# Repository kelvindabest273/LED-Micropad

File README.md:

# LED Micropad
This is a macropad that has 3 keys (Num Lock, Caps Lock, and Scroll Lock), 3 LED indicators for the aforementioned, and a 0.91 inch 128x32 OLED screen that also, you guessed it, shows the status of aforementioned keys!

Render of the macropad:

Front of the case:

Back of the case:

Schematic:

PCB Layout:

BOM: \
1x Seeed XIAO RP2040 \
3x SK6812MINI-E LEDs \
1x EC11 Rotary Encoder \
1x 0.91 OLED 128x32 screen \
3x Cherry MX-style switches \
1x PCB (not sure if this should be included) \
1x 3D Printed Case (not sure if this should be included)

# Resources that I used to help me make this:
I used help from ChatGPT (before you get mad some of this code was like reading an ancient language) \
https://files.seeedstudio.com/wiki/XIAO-RP2040/res/Seeed-Studio-XIAO-RP2040-v1.3.pdf (this one especially) \
https://github.com/HEofOttoman/hackpadbludprintmacro/blob/main/firmware/henrywausbloodyhackbludpad/keyboard.json (and this too) \
https://github.com/hackclub/hackpad/blob/clean/extras/orpheuspad/firmware/QMK/rules.mk \
https://docs.qmk.fm/config_options \
https://docs.qmk.fm/features/oled_driver \
https://docs.qmk.fm/features/led_indicators \
https://docs.qmk.fm/custom_quantum_functions \
https://docs.qmk.fm/features/rgb_matrix \
https://docs.qmk.fm/drivers/ws2812 \
https://docs.qmk.fm/data_driven_config \
https://github.com/Keychron/qmk_firmware/tree/2025q3/keyboards/keychron/v3/ansi/keymaps (just look around here, tho you might not find much here)

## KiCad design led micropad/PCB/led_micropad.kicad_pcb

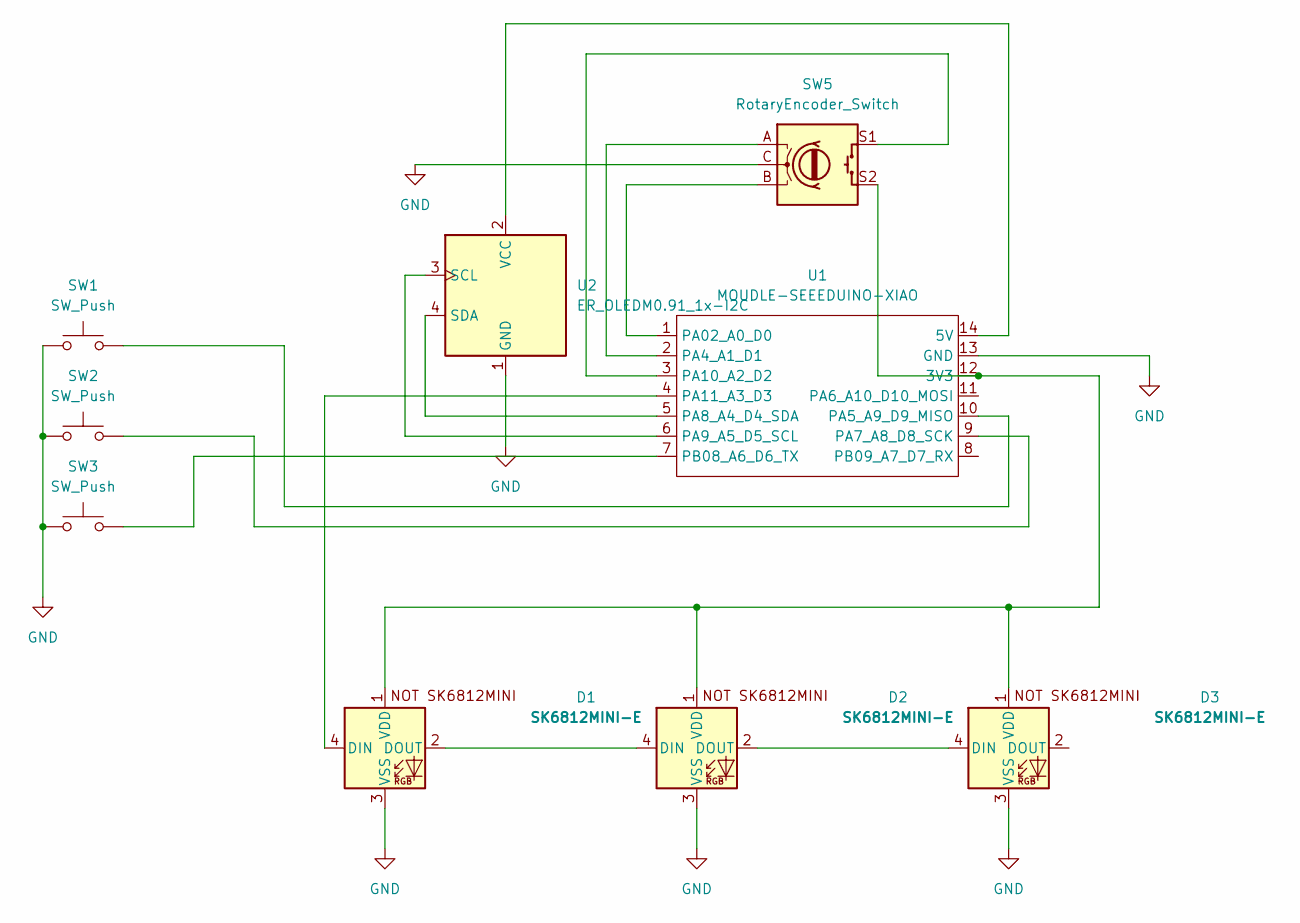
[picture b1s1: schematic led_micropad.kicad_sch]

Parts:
D1, D2, D3: SK6812MINI-E; SK6812MINI-E_fixed
SW1, SW2, SW3: SW_Push; SW_Cherry_MX_1.00u_PCB
SW5: RotaryEncoder_Switch; RotaryEncoder_Alps_EC11E-Switch_Vertical_H20mm
U1: MOUDLE-SEEEDUINO-XIAO; XIAO-Generic-Hybrid-14P-2.54-21X17.8MM
U2: ER_OLEDM0.91_1x-I2C

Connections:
GND: D1.3 (VSS), D2.3 (VSS), D3.3 (VSS), SW1.1, SW2.1, SW3.1, SW5.C, U1.13 (GND), U2.1 (GND)
unnamed: D1.4 (DIN), U1.4 (PA11_A3_D3)
unnamed: D1.2 (DOUT), D2.4 (DIN)
unnamed: D1.1 (VDD), D2.1 (VDD), D3.1 (VDD), SW5.S2, U1.12 (3V3)
unnamed: D2.2 (DOUT), D3.4 (DIN)
unnamed: U1.14 (5V), U2.2 (VCC)
unnamed: SW5.B, U1.1 (PA02_A0_D0)
unnamed: SW5.A, U1.2 (PA4_A1_D1)
unnamed: SW1.2, U1.10 (PA5_A9_D9_MISO)
unnamed: SW2.2, U1.9 (PA7_A8_D8_SCK)
unnamed: U1.5 (PA8_A4_D4_SDA), U2.4 (SDA)
unnamed: U1.6 (PA9_A5_D5_SCL), U2.3 (SCL)
unnamed: SW5.S1, U1.3 (PA10_A2_D2)
unnamed: SW3.2, U1.7 (PB08_A6_D6_TX)

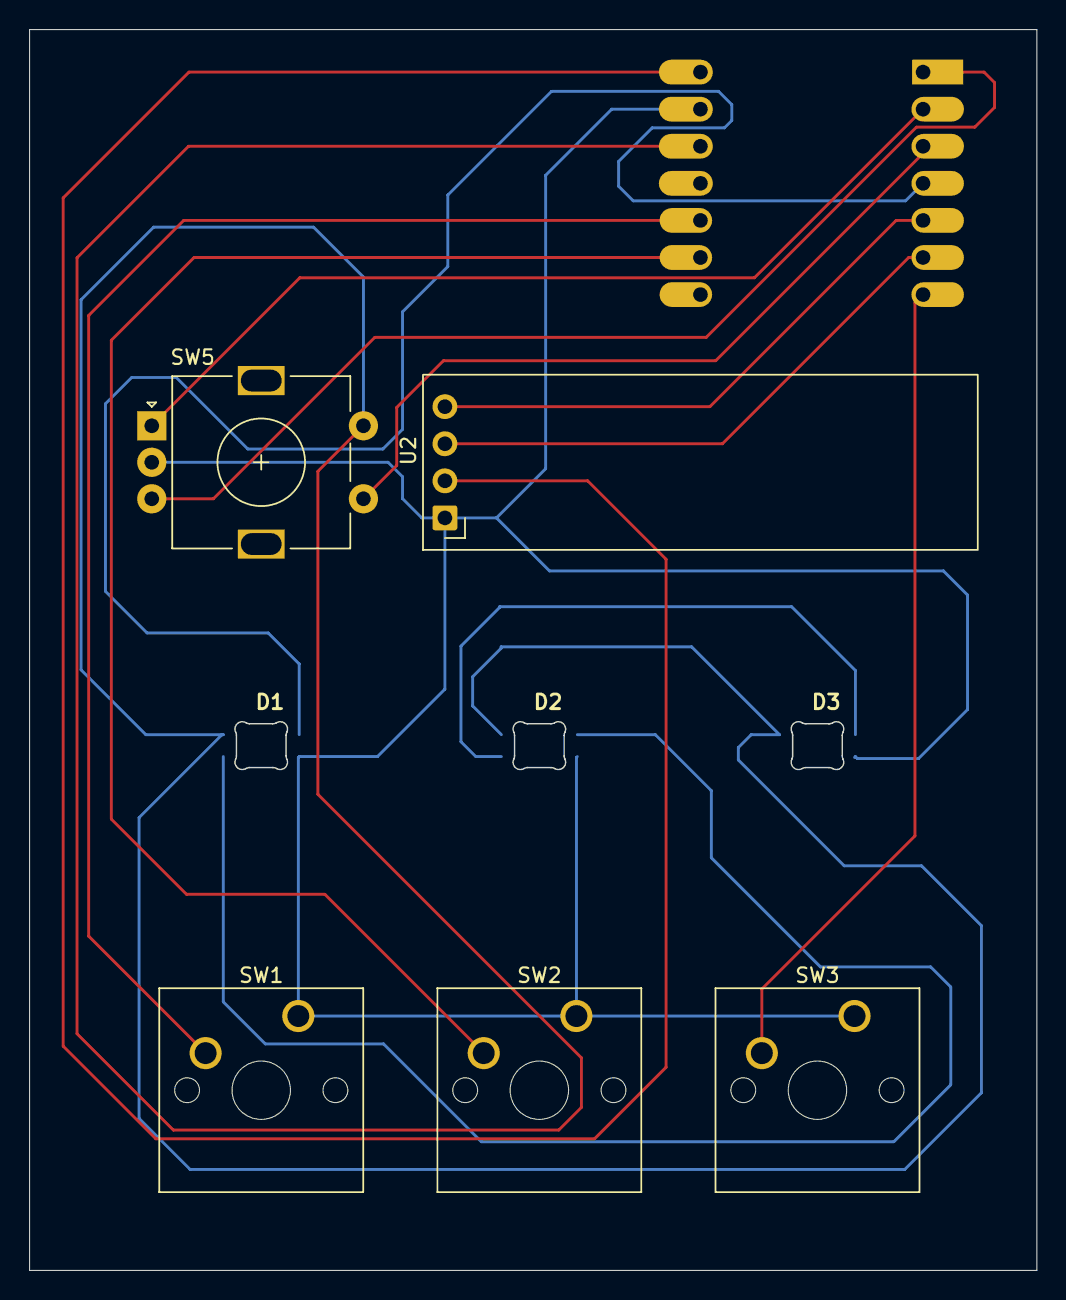
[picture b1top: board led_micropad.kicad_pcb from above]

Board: 2 copper layers, 69.0 x 85.0 mm, 9 parts (1 on the bottom side), 14 nets.
